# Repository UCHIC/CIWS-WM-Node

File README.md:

# CIWS-WM-Node

This repository contains hardware and software designs for a computationally-enabled water meter datalogger. The hardware is made up of two parts. One part is a Raspberry Pi single board computer that serves as the computational resource. The Raspberry Pi is coupled with a data acquisition device that is based on an Arduino Pro and is similar to our simplified datalogger for magnetically-driven residential water meters (See [UCHIC/CIWS-MWM-Logger](https://github.com/UCHIC/CIWS-MWM-Logger)).

The data acquisition device is primarily responsible for processing magnetometer sensor data and storing flow data from the water meter. Secondarily, it controls power to the Raspberry Pi in order to conserve battery life and reduce overall power consumption. Once powered, the Raspberry Pi retreives the flow data and processes it to compute useful summaries of water use, identify water end-uses, or execute other user-defined computational code.

## Structure of this Repository

The 'Firmware' directory contains the firmware for the microcontroller-based data acquisition device, or Datalogger.

The 'Software' directory contains the software for the Raspberry Pi.

The 'Hardware' directory contains hardware design information, including a design and instructions for assembling a Node from off-the-shelf components as well as a printed circuit board (PCB) design and instructions for manufacturing them.

The 'Docs' directory contains documentation.

This device is still under active development.

## Cyberinfrastructure for Intelligent Water Supply (CIWS) 

CIWS is a project funded by the U.S. National Science Foundation to develop cyberinfrastructure for smart water metering and high resolution water-use data collection. We are developing systems for high resolution residential water consumption data collection, processing, and analysis.

## Sponsors and Credits

This work was supported by National Science Foundation Grant [CBET 1552444](https://www.nsf.gov/awardsearch/showAward?AWD_ID=1552444). Any opinions, findings, and conclusions or recommendations expressed in this material are those of the author(s) and do not necessarily reflect the views of the National Science Foundation.

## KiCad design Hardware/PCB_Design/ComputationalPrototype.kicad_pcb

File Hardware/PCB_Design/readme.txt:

This folder contains all the files necessary for manufacturing PCBs.

The `.pro` and `.sch` files are the board layout and schematic respectively. Use these two files with the `.kicad_pcb` file to view the design in kicad.

The `.csv` file and `.zip` files are used for manufaturing the devices. The `.zip` file contains the drill file, gerber files, assembly drawings, and position files. The `.csv` is a list of components used on the device.

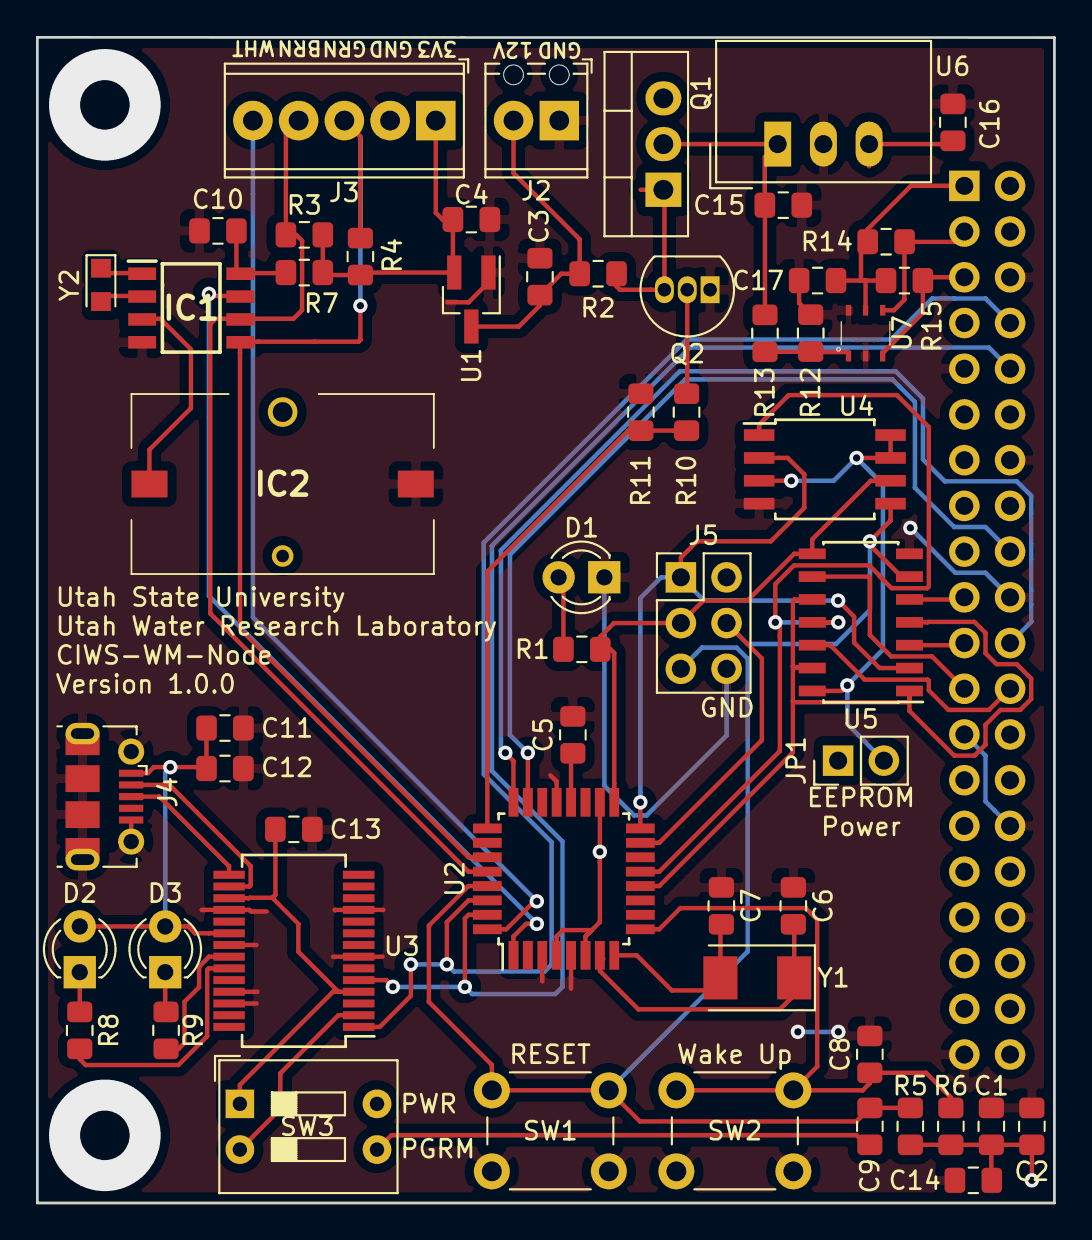
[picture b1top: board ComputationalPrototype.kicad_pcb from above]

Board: 2 copper layers, 56.5 x 64.8 mm, 57 parts (1 on the bottom side), 47 nets.

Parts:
C1, C3, C14, C15, C16: 1uF; C_0805_2012Metric_Pad1.15x1.40mm_HandSolder
C2, C5, C8, C9, C11, C13: 0.1uF; C_0805_2012Metric_Pad1.15x1.40mm_HandSolder
C4: 100uF; C_0805_2012Metric_Pad1.15x1.40mm_HandSolder
C6, C7: 20pF; C_0805_2012Metric_Pad1.15x1.40mm_HandSolder
C10, C12, C17: 10uF; C_0805_2012Metric_Pad1.15x1.40mm_HandSolder
D1, D2, D3: 151031VS06000; LED_D3.0mm_Clear
IC1: PCF8523T_1,118; SOIC127P600X175-8N
IC2: 1072
J1: PinSocket_2x20_P2.54mm_Vertical
J2: 1725656; TerminalBlock_Phoenix_MPT-0,5-2-2.54_1x02_P2.54mm_Horizontal
J3: 1725685; TerminalBlock_Phoenix_MPT-0,5-5-2.54_1x05_P2.54mm_Horizontal
J4: USB_B_Micro; USB_Micro-B_Molex-105017-0001
J5: PinHeader_2x03_P2.54mm_Vertical
JP1: SNT-100-YW-T; PinHeader_1x02_P2.54mm_Vertical
Q1: FQP27P06; TO-220-3_Vertical
Q2: 2N3904; TO-92_Inline
R1, R10: 470; R_0805_2012Metric_Pad1.15x1.40mm_HandSolder
R2, R3, R4, R5, R6, R7, R11: 10k; R_0805_2012Metric_Pad1.15x1.40mm_HandSolder
R8, R9: 1k; R_0805_2012Metric_Pad1.15x1.40mm_HandSolder
R12: 2k; R_0805_2012Metric_Pad1.15x1.40mm_HandSolder
R13: 13k; R_0805_2012Metric_Pad1.15x1.40mm_HandSolder
R14, R15: 5k; R_0805_2012Metric_Pad1.15x1.40mm_HandSolder
SW1, SW2: PTS645SL432LFS; SW_PUSH_6mm
SW3: 1825057-1; SW_DIP_SPSTx02_Slide_9.78x7.26mm_W7.62mm_P2.54mm
U1: MCP1703AT-3302E/CB; SOT-23_Handsoldering
U2: ATmega328P-AU; TQFP-32_7x7mm_P0.8mm
U3: FT232RL; SSOP-28_5.3x10.2mm_P0.65mm
U4: 25LC1024-E/SM; SOIJ-8_5.3x5.3mm_P1.27mm
U5: SN74HC125DR; SOIC-14_3.9x8.7mm_P1.27mm
U6: TSR_1-2450; Converter_DCDC_TRACO_TSR-1_THT
U7: MCP3421A0T-ECH; MCP3425
Y1: F90800021; Crystal_SMD_Abracon_ABM3-2Pin_5.0x3.2mm
Y2: LFXTAL050789REEL; Crystal_SMD_2012-2Pin_2.0x1.2mm_HandSoldering

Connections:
+3V3: C1.1, C2.1, C4.1, C14.1, J3.1, J5.2, JP1.1, R3.1, R4.1, R5.1, R6.1, R7.1, SW3.4, U1.2, U2.4, U2.6, U2.18
+5V: C11.1, C12.1, D2.2, D3.2, J4.1, U3.20
+12V: C3.1, J2.2, Q1.3, R2.1, U1.3
GND: C1.2, C2.2, C3.2, C4.2, C5.2, C6.1, C7.1, C8.2, C10.2, C11.2, C12.2, C13.2, C14.2, C15.2, C16.2, C17.1, D1.1, IC1.4, IC2.2, J1.6, J1.9, J1.14, J1.20, J1.25, J1.30, J1.34, J1.39, J2.1, J3.2, J4.5, J4.6, J5.6, Q2.1, R11.1, R12.1, SW1.2, SW2.2, U1.1, U2.3, U2.5, U2.21, U3.7, U3.11, U3.18, U3.21, U3.25, U3.26, U4.4, U5.7, U6.2, U7.2, U7.6
unnamed: C5.1, U2.20
unnamed: C6.2, U2.7, Y1.1
unnamed: C7.2, U2.8, Y1.2
unnamed: C8.1, R6.2, SW2.1, U2.9
unnamed: C9.1, SW3.3
unnamed: C9.2, J5.5, R5.2, SW1.1, U2.29
unnamed: C10.1, IC1.8, R7.2
unnamed: C13.1, SW3.1, U3.4, U3.17
unnamed: C15.1, Q1.2, R13.2, U6.1
unnamed: C16.1, J1.2, J1.4, U6.3
unnamed: C17.2, J1.1, R14.1, R15.1, U7.5
unnamed: D1.2, R1.2
unnamed: D2.1, R8.1
unnamed: D3.1, R9.1
unnamed: IC1.3, IC2.1
unnamed: J1.3, R14.2, U7.4
unnamed: J1.5, R15.2, U7.3
unnamed: J1.8, U2.30, U3.1
unnamed: J1.10, U2.31, U3.5
unnamed: J1.18, U2.23
unnamed: J1.19, U5.5
unnamed: J1.21, U5.3
unnamed: J1.22, U2.24
unnamed: J1.23, U5.9
unnamed: J1.24, U5.12
unnamed: IC1.5, J3.3, R4.2, U2.27
unnamed: IC1.6, J3.4, R3.2, U2.28
unnamed: J3.5, U2.32
unnamed: J4.2, U3.16
unnamed: J4.3, U3.15
unnamed: J5.1, U2.16, U4.2, U5.2
unnamed: J5.3, R1.1, U2.17, U4.6, U5.8
unnamed: J5.4, U2.15, U4.5, U5.6
unnamed: Q1.1, Q2.3, R2.2
unnamed: Q2.2, R10.1
unnamed: R8.2, U3.23
unnamed: R9.2, U3.22
unnamed: R10.2, R11.2, U2.25
unnamed: R12.2, R13.1, U7.1
unnamed: SW3.2, U3.2
unnamed: U2.12, U5.1, U5.4, U5.10, U5.13
unnamed: U2.13, U4.1, U5.11
VCC: JP1.2, U4.3, U4.7, U4.8, U5.14

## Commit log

2019-11-03 Initial file upload from CIWS-Loggers repo
    Intial move of files from the CIWS-Logger repository and edits to the readme files.
2019-11-03 Update LICENSE
2019-12-16 Updated progress: Shell program for interfacing with the datalogger over SSH
2019-12-16 Fixed firmware bugs
    Missing data records
    Incorrect timestamps
2020-01-04 Updated Software
2020-01-06 Updated to working version
2020-01-25 Bug fixes
2020-05-14 Changed Raspberry Pi power-on logic: will power on every new day to chunk data files by day
2020-05-18 Fixed powerSleep issues
2020-05-19 Fixed bug: ROM data buffer index may go out of bounds
2020-05-20 Fixing auto turn-off condition
2020-05-20 Attempting to fix issue #1
2020-06-10 Merging develop into master branch
2020-06-20 Added comments to denote where HTTPS POST request code should be called
2020-07-03 Renamed README.md to be consistent with the rest of the repository
2020-07-03 Updating README.md
2020-07-03 Creating a documentation README.md
2020-07-03 Renaming readme.md to README.md for consistency for the rest of the repository
2020-07-09 Reorganized Documentation
2020-07-09 Added WM-Node off-the-shelf build instructions
2020-07-09 Added documentation .docx files
2020-08-01 Added clarifying information in OTS build instructions
2020-08-01 Added functionality to set which data sets to transmit (still needs to be tested)
2020-08-05 Add files via upload
    Stitched the disaggregation code, tranmision code, and user transmission selection code together. Untested.
2020-08-07 Added function declarations to PyMethodDef methods[] on line 572
2020-08-07 Added settings for determining which datasets to store on the device
2020-09-02 Update README.md
    Added NSF award badge to readme.
2020-09-22 Add files via upload
    Updating to Python3
2020-09-22 Update bashrc
2020-09-23 Rename processData.py to saveData.py
2020-09-23 Rename processData.py to crunchData.py
2020-11-18 Update replaceC.py
    Output file date strings are now ISO 8601 compliant
2020-12-01 Rename Software/rc.local to Software/setup/rc.local
2020-12-01 Rename Software/bashrc to Software/setup/bashrc
2020-12-01 Rename Software/cmdline.txt to Software/setup/cmdline.txt
2020-12-01 Rename Software/config.txt to Software/setup/config.txt
2021-06-15 Rename Node.csv to PartsList.csv
2021-06-15 Rename readme.txt to readme.md
2021-06-15 Rename readme.md to README.md
2021-06-16 Rename Hardware/Buildinstructions.txt to Hardware/Off-The-Shelf/Buildinstructions.txt
